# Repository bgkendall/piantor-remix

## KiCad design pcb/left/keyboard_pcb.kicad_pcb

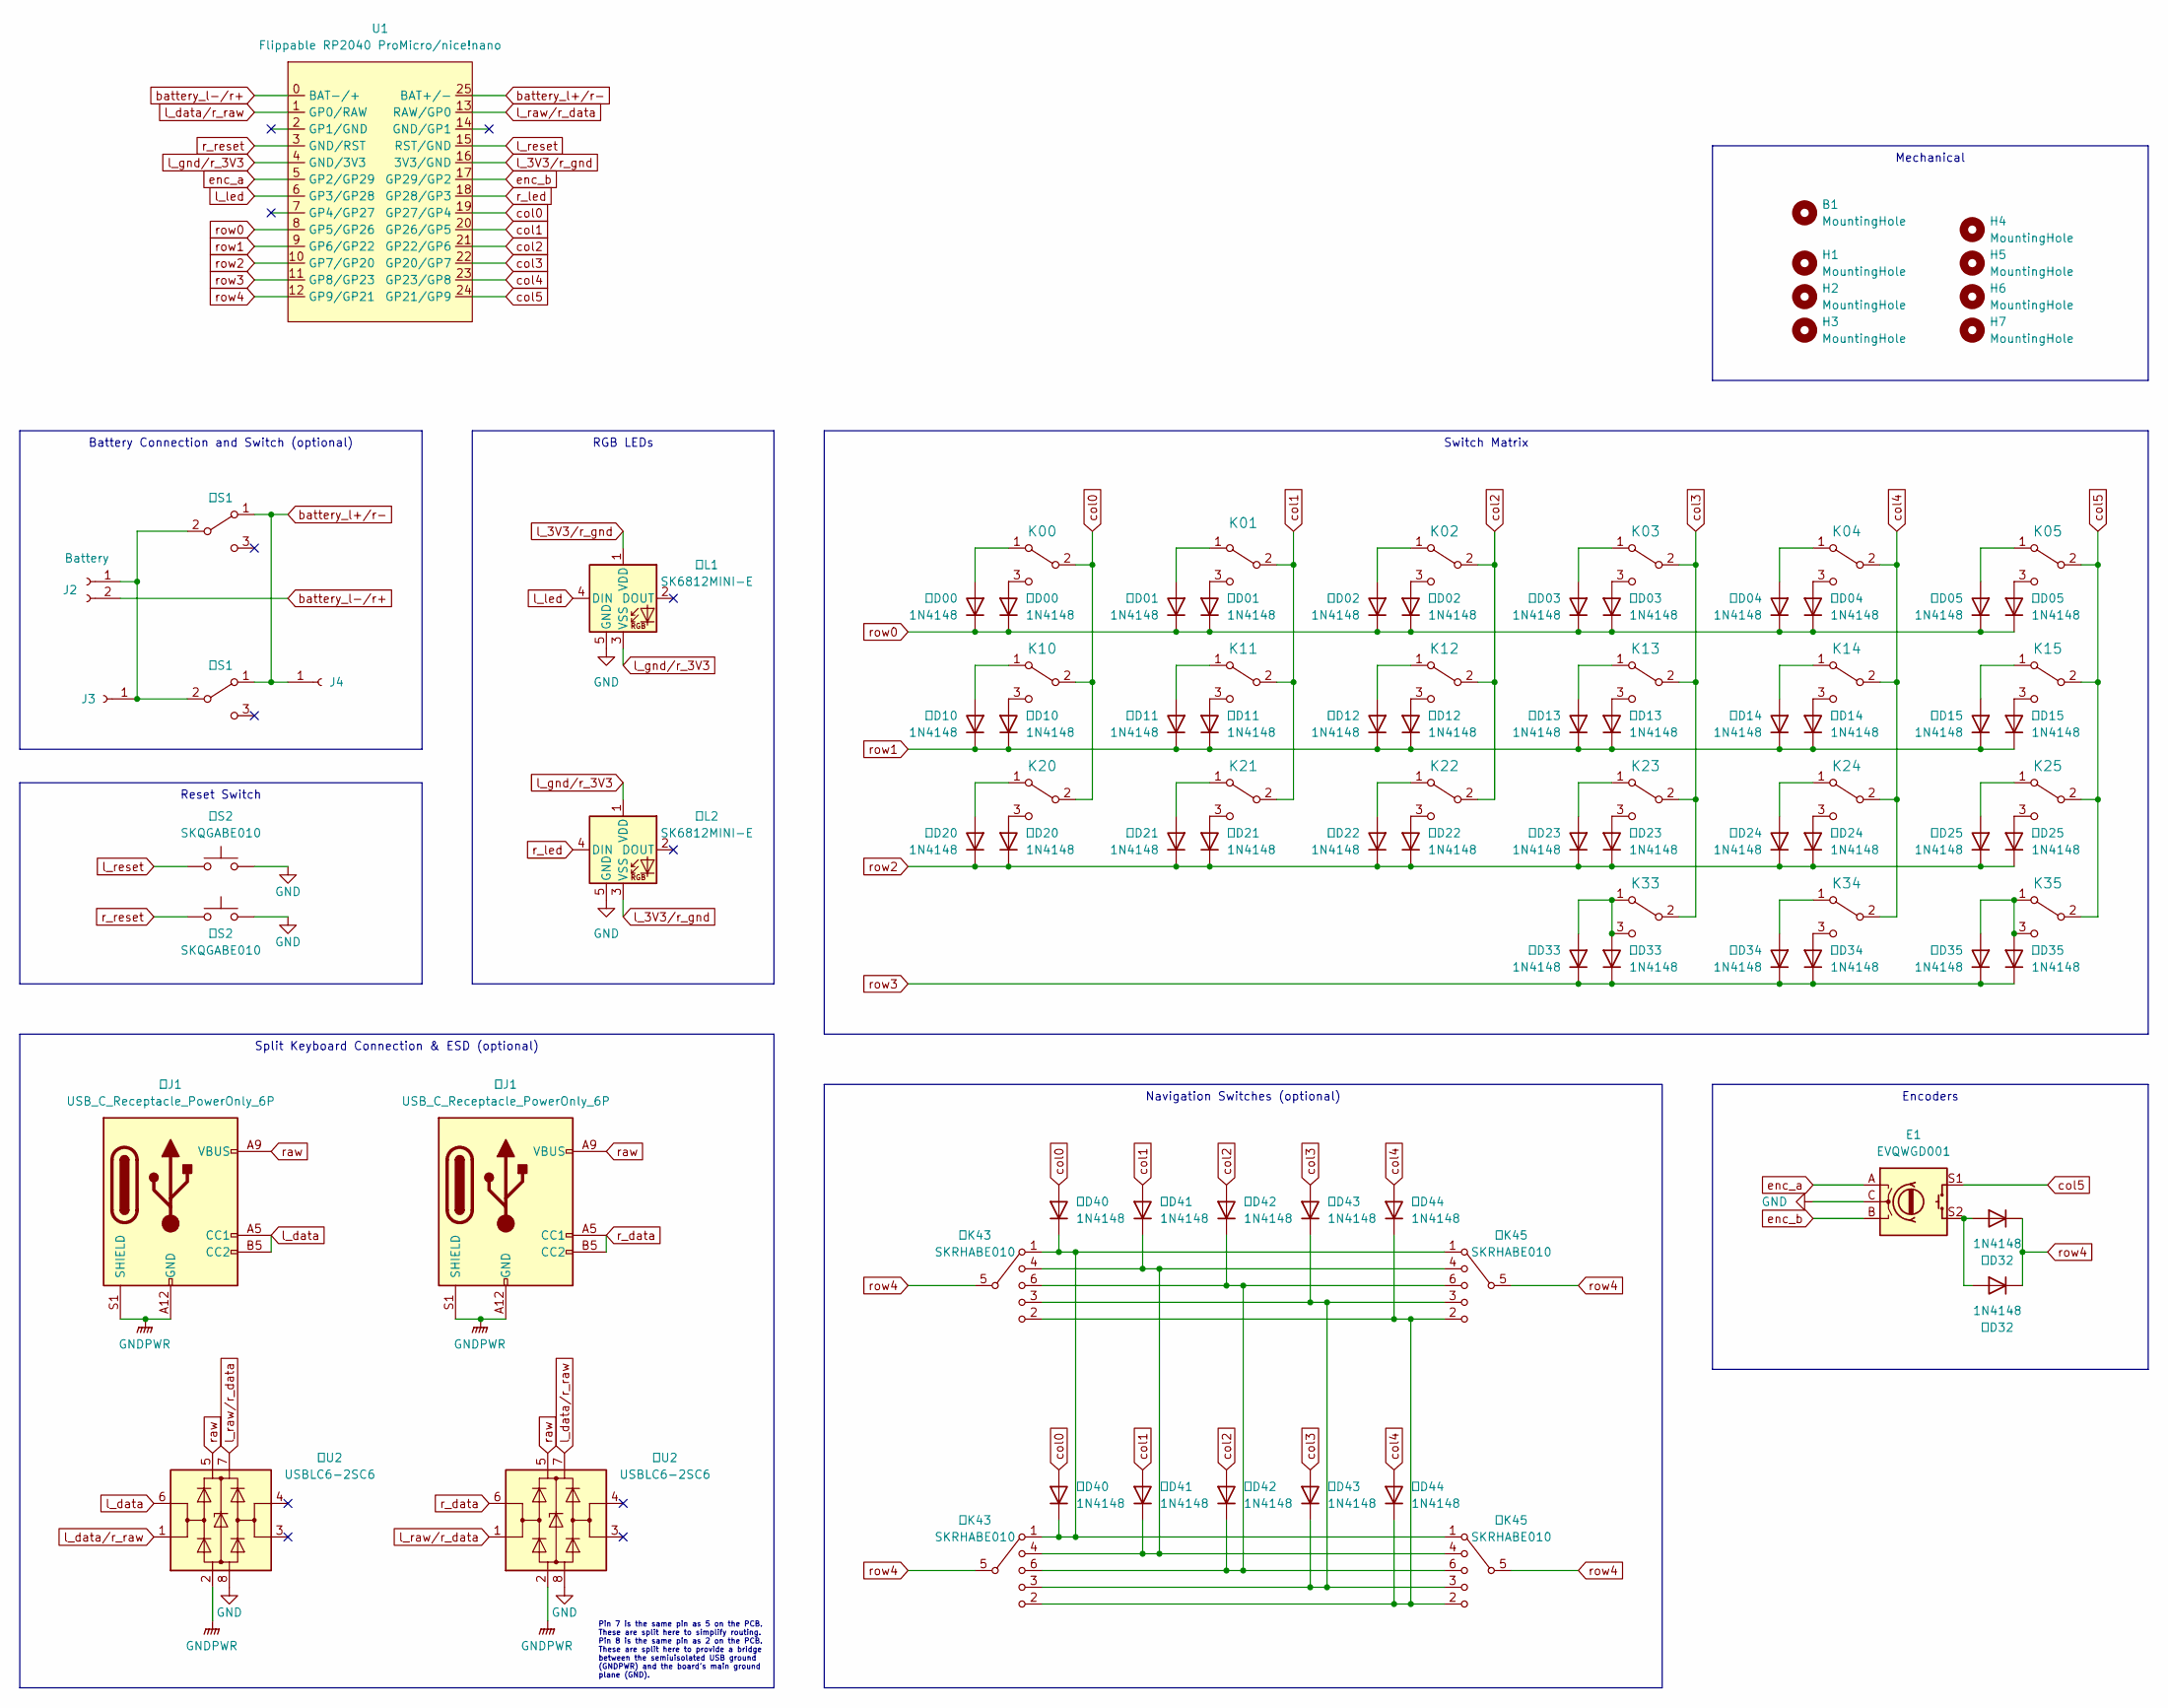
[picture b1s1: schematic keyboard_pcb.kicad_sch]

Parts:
B1: MountingHole; Battery_Cutout_401020
E1: EVQWGD001; RollerEncoder_Panasonic_EVQWGD001_Reversible
H1, H2, H3, H4, H5, H6, H7: MountingHole; MountingHole_2.2mm_M2
J2: Battery; SolderWire-0.127sqmm_1x02_P3.7mm_D0.48mm_OD1mm
J3, J4: Conn_01x01_Socket; SolderWire-0.127sqmm_1x01_D0.48mm_OD1mm
K00, K01, K10, K11, K20, K21: KEYSW; SW_choc_v1_HS_1u_Reversible_Opposing
K02, K03, K04, K05, K12, K13, K14, K15, K22, K23, K24, K25, K33, K34, K35: KEYSW; SW_choc_v1_HS_1u_Reversible
U1: Flippable RP2040 ProMicro/nice!nano; ProMicro_Battery_Reversible
右D00, 右D01, 右D02, 右D03, 右D04, 右D05, 右D10, 右D11, 右D12, 右D13, 右D14, 右D15, 右D20, 右D21, 右D22, 右D23, 右D24, 右D25, 右D32, 右D33, 右D34, 右D35: 1N4148; D_SOD-123; LCSC C7603179
右D40, 右D41, 右D42, 右D43, 右D44: 1N4148; D_SOD-123_Centre_Label; LCSC C7603179
右J1: USB_C_Receptacle_PowerOnly_6P; CUI_UJC-HP-L-G-5-MSMT-TR_Reversible_Optional; LCSC C2858274
右K43, 右K45: SKRHABE010; Nav_Switch_SKRHAxE010; LCSC C139794
右L2: SK6812MINI-E; SK6812-MINI-E_Jumped_GND
右S1: SW_SPST; SW_SPDT_PCM12_Reversible
右S2: SKQGABE010; SW_SPST_SKQG_WithStem; LCSC C115351
右U2: USBLC6-2SC6; SOT-23-6_Handsoldering_Split_VCC_GND
左D00, 左D01, 左D02, 左D03, 左D04, 左D05, 左D10, 左D11, 左D12, 左D13, 左D14, 左D15, 左D20, 左D21, 左D22, 左D23, 左D24, 左D25, 左D32, 左D33, 左D34, 左D35: 1N4148; D_SOD-123; LCSC C7603179
左D40, 左D41, 左D42, 左D43, 左D44: 1N4148; D_SOD-123_Centre_Label; LCSC C7603179
左J1: USB_C_Receptacle_PowerOnly_6P; CUI_UJC-HP-L-G-5-MSMT-TR_Reversible_Optional; LCSC C2858274
左K43, 左K45: SKRHABE010; Nav_Switch_SKRHAxE010; LCSC C139794
左L1: SK6812MINI-E; SK6812-MINI-E_Jumped_GND
左S1: SW_SPST; SW_SPDT_PCM12_Reversible
左S2: SKQGABE010; SW_SPST_SKQG_WithStem; LCSC C115351
左U2: USBLC6-2SC6; SOT-23-6_Handsoldering_Split_VCC_GND

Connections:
GND: E1.C, 右L2.5 (GND), 右S2.1, 右U2.8 (GND_OUT), 左L1.5 (GND), 左S2.1, 左U2.8 (GND_OUT)
GNDPWR: 右J1.A12 (GND), 右J1.B12 (GND), 右J1.S1 (SHIELD), 右U2.2 (GND_IN), 左J1.A12 (GND), 左J1.B12 (GND), 左J1.S1 (SHIELD), 左U2.2 (GND_IN)
unnamed: J2.1, J3.1, 右S1.2 (B), 左S1.2 (B)
unnamed: K00.1 (A), 左D00.2 (A)
unnamed: K00.3 (C), 右D00.2 (A)
unnamed: K01.1 (A), 左D01.2 (A)
unnamed: K01.3 (C), 右D01.2 (A)
unnamed: K02.1 (A), 左D02.2 (A)
unnamed: K02.3 (C), 右D02.2 (A)
unnamed: K03.1 (A), 左D03.2 (A)
unnamed: K03.3 (C), 右D03.2 (A)
unnamed: K04.1 (A), 左D04.2 (A)
unnamed: K04.3 (C), 右D04.2 (A)
unnamed: K05.1 (A), 左D05.2 (A)
unnamed: K05.3 (C), 右D05.2 (A)
unnamed: K10.1 (A), 左D10.2 (A)
unnamed: K10.3 (C), 右D10.2 (A)
unnamed: K11.1 (A), 左D11.2 (A)
unnamed: K11.3 (C), 右D11.2 (A)
unnamed: K12.1 (A), 左D12.2 (A)
unnamed: K12.3 (C), 右D12.2 (A)
unnamed: K13.1 (A), 左D13.2 (A)
unnamed: K13.3 (C), 右D13.2 (A)
unnamed: K14.1 (A), 左D14.2 (A)
unnamed: K14.3 (C), 右D14.2 (A)
unnamed: K15.1 (A), 左D15.2 (A)
unnamed: K15.3 (C), 右D15.2 (A)
unnamed: K20.1 (A), 左D20.2 (A)
unnamed: K20.3 (C), 右D20.2 (A)
unnamed: K21.1 (A), 左D21.2 (A)
unnamed: K21.3 (C), 右D21.2 (A)
unnamed: K22.1 (A), 左D22.2 (A)
unnamed: K22.3 (C), 右D22.2 (A)
unnamed: K23.1 (A), 左D23.2 (A)
unnamed: K23.3 (C), 右D23.2 (A)
unnamed: K24.1 (A), 左D24.2 (A)
unnamed: K24.3 (C), 右D24.2 (A)
unnamed: K25.1 (A), 左D25.2 (A)
unnamed: K25.3 (C), 右D25.2 (A)
unnamed: K33.1 (A), K33.3 (C), 右D33.2 (A), 左D33.2 (A)
unnamed: K34.1 (A), 左D34.2 (A)
unnamed: K34.3 (C), 右D34.2 (A)
unnamed: K35.1 (A), K35.3 (C), 右D35.2 (A), 左D35.2 (A)
unnamed: E1.S2, 右D32.2 (A), 左D32.2 (A)
unnamed: 右D40.1 (K), 右K43.1 (A), 右K45.1 (A), 左D40.1 (K), 左K43.1 (A), 左K45.1 (A)
unnamed: 右D41.1 (K), 右K43.4 (B), 右K45.4 (B), 左D41.1 (K), 左K43.4 (B), 左K45.4 (B)
unnamed: 右D42.1 (K), 右K43.6 (D), 右K45.6 (D), 左D42.1 (K), 左K43.6 (D), 左K45.6 (D)
unnamed: 右D43.1 (K), 右K43.3 (C), 右K45.3 (C), 左D43.1 (K), 左K43.3 (C), 左K45.3 (C)
unnamed: 右D44.1 (K), 右K43.2 (Ctr), 右K45.2 (Ctr), 左D44.1 (K), 左K43.2 (Ctr), 左K45.2 (Ctr)
battery_l+/r-: J4.1, U1.25 (BAT+/-), 右S1.1 (A), 左S1.1 (A)
battery_l-/r+: J2.2, U1.0 (BAT-/+)
col0: K00.2 (B), K10.2 (B), K20.2 (B), U1.19 (GP27/GP4), 右D40.2 (A), 左D40.2 (A)
col1: K01.2 (B), K11.2 (B), K21.2 (B), U1.20 (GP26/GP5), 右D41.2 (A), 左D41.2 (A)
col2: K02.2 (B), K12.2 (B), K22.2 (B), U1.21 (GP22/GP6), 右D42.2 (A), 左D42.2 (A)
col3: K03.2 (B), K13.2 (B), K23.2 (B), K33.2 (B), U1.22 (GP20/GP7), 右D43.2 (A), 左D43.2 (A)
col4: K04.2 (B), K14.2 (B), K24.2 (B), K34.2 (B), U1.23 (GP23/GP8), 右D44.2 (A), 左D44.2 (A)
col5: E1.S1, K05.2 (B), K15.2 (B), K25.2 (B), K35.2 (B), U1.24 (GP21/GP9)
enc_a: E1.A, U1.5 (GP2/GP29)
enc_b: E1.B, U1.17 (GP29/GP2)
l_3V3/r_gnd: U1.16 (3V3/GND), 右L2.3 (VSS), 左L1.1 (VDD)
l_data: 左J1.A5 (CC1), 左J1.B5 (CC2), 左U2.6 (I/O1)
l_data/r_raw: U1.1 (GP0/RAW), 右U2.7 (VBUS_OUT), 左U2.1 (I/O1)
l_gnd/r_3V3: U1.4 (GND/3V3), 右L2.1 (VDD), 左L1.3 (VSS)
l_led: U1.6 (GP3/GP28), 左L1.4 (DIN)
l_raw/r_data: U1.13 (RAW/GP0), 右U2.1 (I/O1), 左U2.7 (VBUS_OUT)
l_reset: U1.15 (RST/GND), 左S2.2
r_data: 右J1.A5 (CC1), 右J1.B5 (CC2), 右U2.6 (I/O1)
r_led: U1.18 (GP28/GP3), 右L2.4 (DIN)
r_reset: U1.3 (GND/RST), 右S2.2
raw: 右J1.A9 (VBUS), 右J1.B9 (VBUS), 右U2.5 (VBUS_IN), 左J1.A9 (VBUS), 左J1.B9 (VBUS), 左U2.5 (VBUS_IN)
row0: U1.8 (GP5/GP26), 右D00.1 (K), 右D01.1 (K), 右D02.1 (K), 右D03.1 (K), 右D04.1 (K), 右D05.1 (K), 左D00.1 (K), 左D01.1 (K), 左D02.1 (K), 左D03.1 (K), 左D04.1 (K), 左D05.1 (K)
row1: U1.9 (GP6/GP22), 右D10.1 (K), 右D11.1 (K), 右D12.1 (K), 右D13.1 (K), 右D14.1 (K), 右D15.1 (K), 左D10.1 (K), 左D11.1 (K), 左D12.1 (K), 左D13.1 (K), 左D14.1 (K), 左D15.1 (K)
row2: U1.10 (GP7/GP20), 右D20.1 (K), 右D21.1 (K), 右D22.1 (K), 右D23.1 (K), 右D24.1 (K), 右D25.1 (K), 左D20.1 (K), 左D21.1 (K), 左D22.1 (K), 左D23.1 (K), 左D24.1 (K), 左D25.1 (K)
row3: U1.11 (GP8/GP23), 右D33.1 (K), 右D34.1 (K), 右D35.1 (K), 左D33.1 (K), 左D34.1 (K), 左D35.1 (K)
row4: U1.12 (GP9/GP21), 右D32.1 (K), 右K43.5 (Com), 右K45.5 (Com), 左D32.1 (K), 左K43.5 (Com), 左K45.5 (Com)

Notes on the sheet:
Reset Switch
RGB LEDs
Encoders
Mechanical
Switch Matrix
Navigation Switches (optional)
Split Keyboard Connection & ESD (optional)
Battery Connection and Switch (optional)
Pin 7 is the same pin as 5 on the PCB. These are split here to simplify routing. Pin 8 is the same pin as 2 on the PCB. These are split here to provide a bridge between the semiuisolated USB ground (GNDPWR) and the board’s main ground plane (GND).

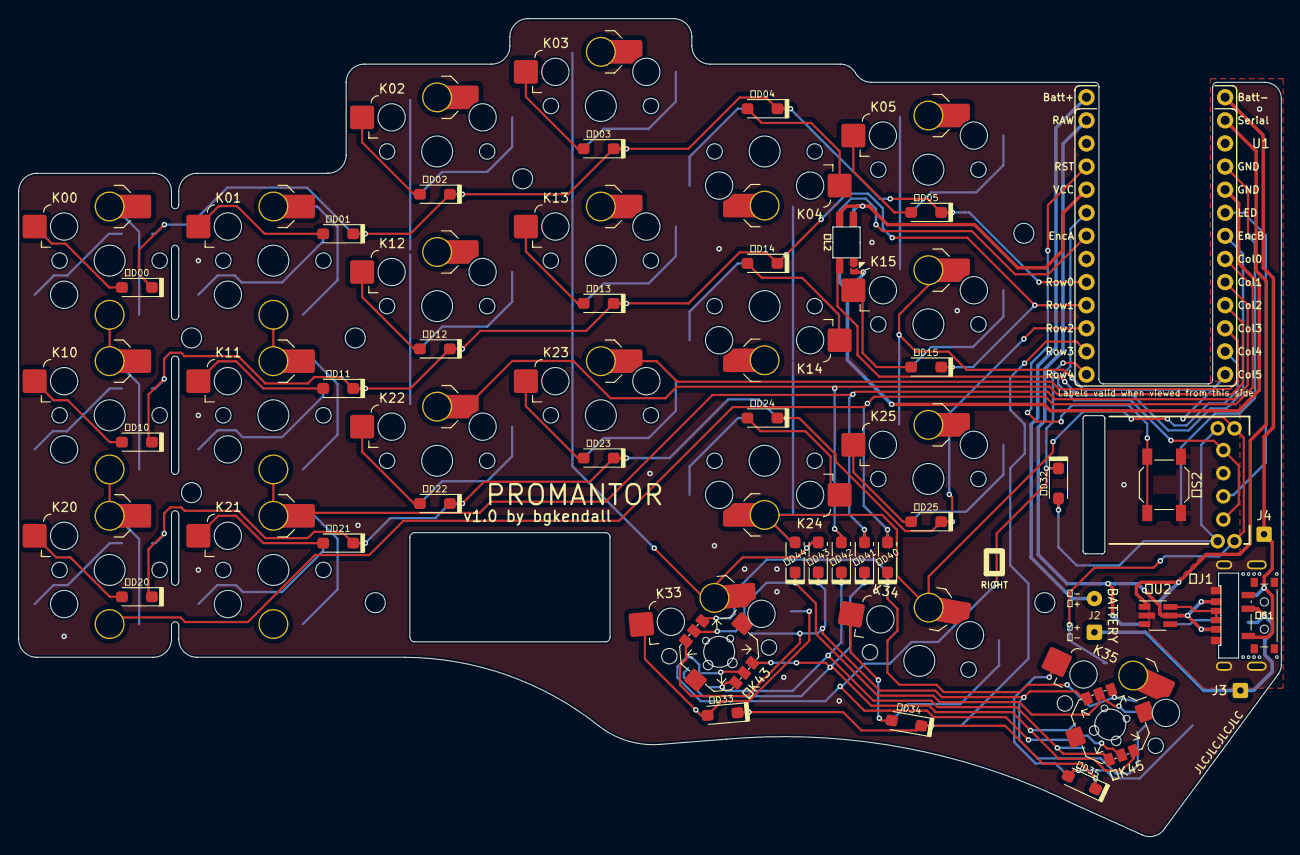
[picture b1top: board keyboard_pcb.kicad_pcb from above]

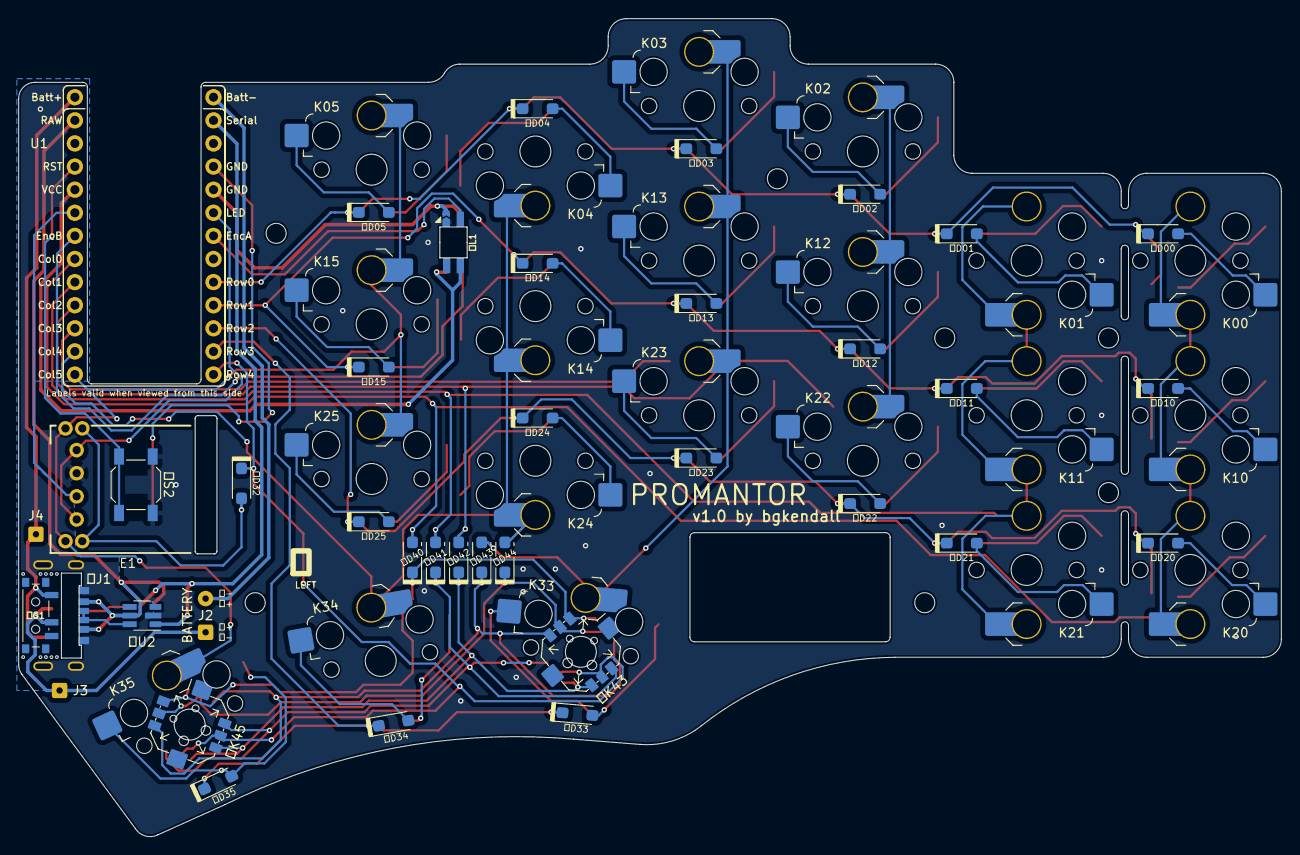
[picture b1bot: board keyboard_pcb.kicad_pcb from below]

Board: 2 copper layers, 138.8 x 89.9 mm, 102 parts (34 on the bottom side), 75 nets.

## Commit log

2024-02-09 Update files to KiCad 7
2024-02-09 Remove VBUS sense
2024-02-09 Updated schematic
    * Replace Pico with Pro Micro
    * Copy ProMicro footprint from [marbastlib](https://github.com/ebastler/marbastlib) and update with flipped pin labels
    * Add battery connections
    * Add RGB LED
    * Add reset switch
    * Switch split keyboard connection from audio jack to USB C
2024-02-09 Update matrix schematic
    * Add diodes
    * Add 5-way nav. switches
    * Duplicate left to right
    * Tidy layout
2024-02-10 Update nav. switch symbol to match datasheet
    https://www.mouser.com/datasheet/2/15/SKRH-1370966.pdf
2024-02-10 Add nav. switch footprint based on datasheet
    [SKRHAxE010](https://www.mouser.com/datasheet/2/15/SKRH-1370966.pdf)
2024-02-10 Tweak nav. switch footprint
2024-02-10 Add roller encoder footprint
    [rollyboi9000000](https://github.com/howardt12345/rollyboi9000000)
    See [note on pinout](https://github.com/rcuquemelle/EVQWGD001-Pinout/blob/main/README.md)
2024-02-10 Add slide switch footprint
    SW_MSK12C02 from [marbastlib](https://github.com/ebastler/marbastlib/blob/main/footprints/marbastlib-various.pretty/SW_MSK12C02-HB.kicad_mod)
    Right guide boss is removed to allow two switches to be placed on opposite sides of a PCB without duplicate drill holes
2024-02-10 Add 6-pin USB C socket footprint
    Copied from KiCad library
    Right mounting holes are removed to allow two socket footprints to be placed on opposite sides of a PCB without duplicate holes
2024-02-10 Add project’s Keebio Parts library
2024-02-10 Assign footprints
    TODO:
    * Reassign mounting holes — these seem to have been renamed, so the schematic no longer matches the linked library
    * Create mirrorable MCU footprint
    * Decide on reset switch
    * Create mirrorable hot-swap switch footprint(s)
2024-02-10 Fix mounting holes
    There were two H1s and three H4s! Add H5–7 and assign M2 mounting hole from KiCad library (no visible change noticed when updating on PCB).
2024-02-10 Fix pin numbering for SK6812MINI-E
    The “E” has a different [pinout](https://cdn-shop.adafruit.com/product-files/4960/4960_SK6812MINI-E_REV02_EN.pdf) to the non-“E”
2024-02-12 Tweak schematic
    * Change power switches to SP**D**T to match MSK12C02
    * Switch from double-named nets to single name that covers both orientations
    * Update flippable ProMicro symbol to remove gaps between pins that are no longer needed
    * Wire connection to ground through SK6812 GND leg, which will act as a jumper
2024-02-13 Update battery connections, etc.
    * Add THT option for battery connection
    * Add THT option for external power switch
    * Rationalise circuit for battery connections and switches
    * Add mouse bites for switch panel
    * Use Molex Pico-EZmate connector for battery (other connectors are too tall)
    * Simplify circuit diagram for reset switch
2024-02-13 Simplify keyboard matrix
    * Remove right-hand keys (left-hand keys will be made reversible)
    * Add right hand diodes into left-hand (now common) matrix
    * Move encoders into own group
    * Move navigation switches into own group
    * Swap encoder A and left LED pins on MCU (so that encoder pins are together), move right LED pin to be opposite left LED pin
    * Wire split keyboard ground pins to GND
2024-02-13 Indicate diode type
2024-02-13 Add bespoke diode footprint
2024-02-13 Update names of project symbol and footprint libraries
2024-02-13 Add descriptions to custom footprints and adjust arrows in nav. switch footprint
2024-02-13 Round corners of SK6812 footprint to match other footprints
2024-02-13 Add reversible hot-swap choc footprint
2024-02-13 Renumber thumb keys to match new schematic
2024-02-13 Rotate switch footprint to fit board
2024-02-13 Add alternate reversible switch footprint
2024-02-13 Tweak switch footprint
2024-02-13 Assign new switch footprints
2024-02-13 Un-mirror switches
2024-02-17 Use CUI Devices USB receptacle for board-to-board connection
    [Model UJC-HP-L-G-5-MSMT-TR](https://www.cuidevices.com/product/resource/ujc-hp-l-g-5-msmt-tr.pdf)
2024-02-18 Base slide switch on KiCad library version
2024-02-18 Assign reset button footprint and remove unneeded mouse-bite symbols
2024-02-18 Change roller encoder to reversible version
2024-02-18 Add battery cut-out
2024-02-19 Tweak footprint for USB socket
    That location on the board will either have the mid-mount USB socket (wired boards) or the power switch (wireless boards). Since the mid-mount socket requires a cut-out but the switch does not, the s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
2024-02-19 Fix minor issues and footprint assignments
2024-02-19 Clean PCB
    * Remove all tracks and vias
    * Remove VBUS detect resistors
2024-02-19 Update PCB from schematic
    * Rotate switches as needed
    * Flip all lefthand footprints to back
    * Fix minor alignment issue in USB socket
2024-02-19 Position key switch diodes and nav. switches, tweak footprint silkscreens
2024-02-19 Make SK6812 footprint cut-out reversible
    Overlapping cut-outs do not seem to work, so each side now has just half the cut-out outline.
2024-02-19 Minor footprint tweaks
2024-02-19 Encoder B pin is now opposite Encoder A
    This should mean that the pins will actually work out the same when the board is flipped.
2024-02-19 Replaced RP Pico with Pro Micro/nice!nano footprint
    For space reasons, the MCU will be mounted immediately under the main PCB (with no standoffs) with the USB port facing upwards. This requires a cut-out in the PCB to allow space for the USB port and 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
2024-02-19 Fix 3D model location for switches
2024-02-19 Rough layout of all components, split switch jumper into two jumpers
2024-02-19 Prevent switch labels from being covered by hot-swap socket
2024-02-20 Fillet battery cut-out
2024-02-20 Add outlines of Piantor and Piantor Pro cases and align USB ports as needed
2024-02-20 Various tweaks
    * Assign `PWR` net class to battery connections
    * Change `PWR` net class witch to 3.8mm for more routing options around USB ports and power switch
    * Renumber sockets so that the USB ports are ×J1, and the power connections start at J2
    * Remove the switch access point that is duplicated by pin 1 of the alternate battery connection
    * Change reset switch to the smaller B3U-1000P-B (this may change again as that one is a bit pricey for a reset switch)
    * Move reset switch to be near reset pin
2024-02-20 Assign “battery_l+/r-” to PWT net class
2024-02-20 Adjust silkscreen on ProMicro footprint
2024-02-20 Make USB port GND connections solid
2024-02-20 Add net class flag to “battery_l+/r-”
2024-02-20 Add tracks for power and related nets, update footprints
2024-02-20 Rotate nav. switches so that pins 4–6 are not right next to a hot-swap pad on the same side
2024-02-20 Connect encoder to MCU, separate left and right side encoder switch to diode connection
2024-02-20 Add tracks connecting rows and columns to MCU, swap LED and Encoder pins for ease of routing
2024-02-20 Further routing tweaks
2024-02-21 Tweak orientation of nav. switches and put them on the correct side
2024-02-21 Connect left and right nav. switch nets to allow for easier routing
2024-02-21 Initial routing of nav. switches
2024-02-21 Move encoder diode outside encoder footprint
    Want to add a standoff under the encoder, so can’t have a component there!
    Updated schematic between encoder and diode to simplify routing.
2024-02-21 Connected columns
2024-02-21 Connect rows
2024-02-21 Remove mouse bites
2024-02-21 Minor routing tweaks
2024-02-21 Clean up a few DRC errers
2024-02-21 Add datasheets for reference
2024-02-21 Update switch footprints to remove courtyard errors from DRC
2024-02-21 Fix silkscreen warnings reported by DRC
2024-02-21 Update reversible hot-swap footprint to wrap pad around hole rather than colliding
2024-02-22 Reduce size of MCU keep-out, fit silkscreen issues
2024-02-22 Update matrix to remove missing connections
    The switch side of lefthand diodes no longer need to connect righthand diodes. Diodes join to the same row trace, but the switch-to-diode connections are separate (except for the switches that overla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
2024-02-22 Fix ground plane and some minor changes
    * Add vias to fix all ground plane disconnects reported by DRC
    * Change reset switch part
    * Add reference to backside of encoder
    * Fix broken line on encoder silkscreen
    * Fix footprint type for SK6812-MINI-E
2024-02-23 Minor tweaks
    * Improve ground plane
    * Improve SK6812 jumper pin
    * Add silkscreen enclosing bottom 12 pins of MCU
2024-02-23 Tweak routing
    Also, ensure that ground planes are connected if outer column removed
2024-02-25 Update some silkscreening and a minor routing tweak
2024-02-25 Change footprints for wire connections
2024-02-25 Add version silkscreen
2024-02-25 Fix track positions undone by previous change
2024-02-25 Add alt. battery socket and JLC order number silkscreens
2024-03-26 Update track routing
2024-04-07 Add non-optional (reversible only) version of mid-mount USB C socket
2024-04-07 Change shield pins to match schematic symbol
2024-05-05 Part updates
    * Add LCSC part number property to various parts
    * Update Value for various parts
    * Use SKQGABE010 for reset instead of KXT3
    * Move reset switches to under encoder to accommodate larger switch footprint
    * Re-route reset tracks and some nearby tracks
    * Tweak silkscreens
2024-05-05 Remove Pico-EZmate connector for battery
    The battery terminals can be (carefully) soldered to the board. This is going to be far easier (and cheaper!) than trying to crimp the EZmate terminals (at least without the correct tools).
2024-05-11 Fix various DRC errors
2024-05-11 Add ESD protection to USB port
    A pair (left and right) of USBLC6 chips have been added. The USB port now has its own ground plane that is somewhat isolated from the main board ground and only connected at the USBLC6 ground pads.
2024-06-12 Update to KiCad v8
2024-06-12 Basic colour assignments to nets
2024-06-12 Add track separation
    Add separation between parallel tracks where possible.
    Add additional ground vias to increase ground plane coverage.
    Reroute reset line to minimise running parallel to signal tracks.
2024-06-12 Simplify reset routing
    The reset switches do not need to be coupled at all. Simply connect the lefthand reset switch to the left RST pin and the ground plane, and similarly on the righthand side. We don’t need to route and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
2024-12-17 Update project settings
